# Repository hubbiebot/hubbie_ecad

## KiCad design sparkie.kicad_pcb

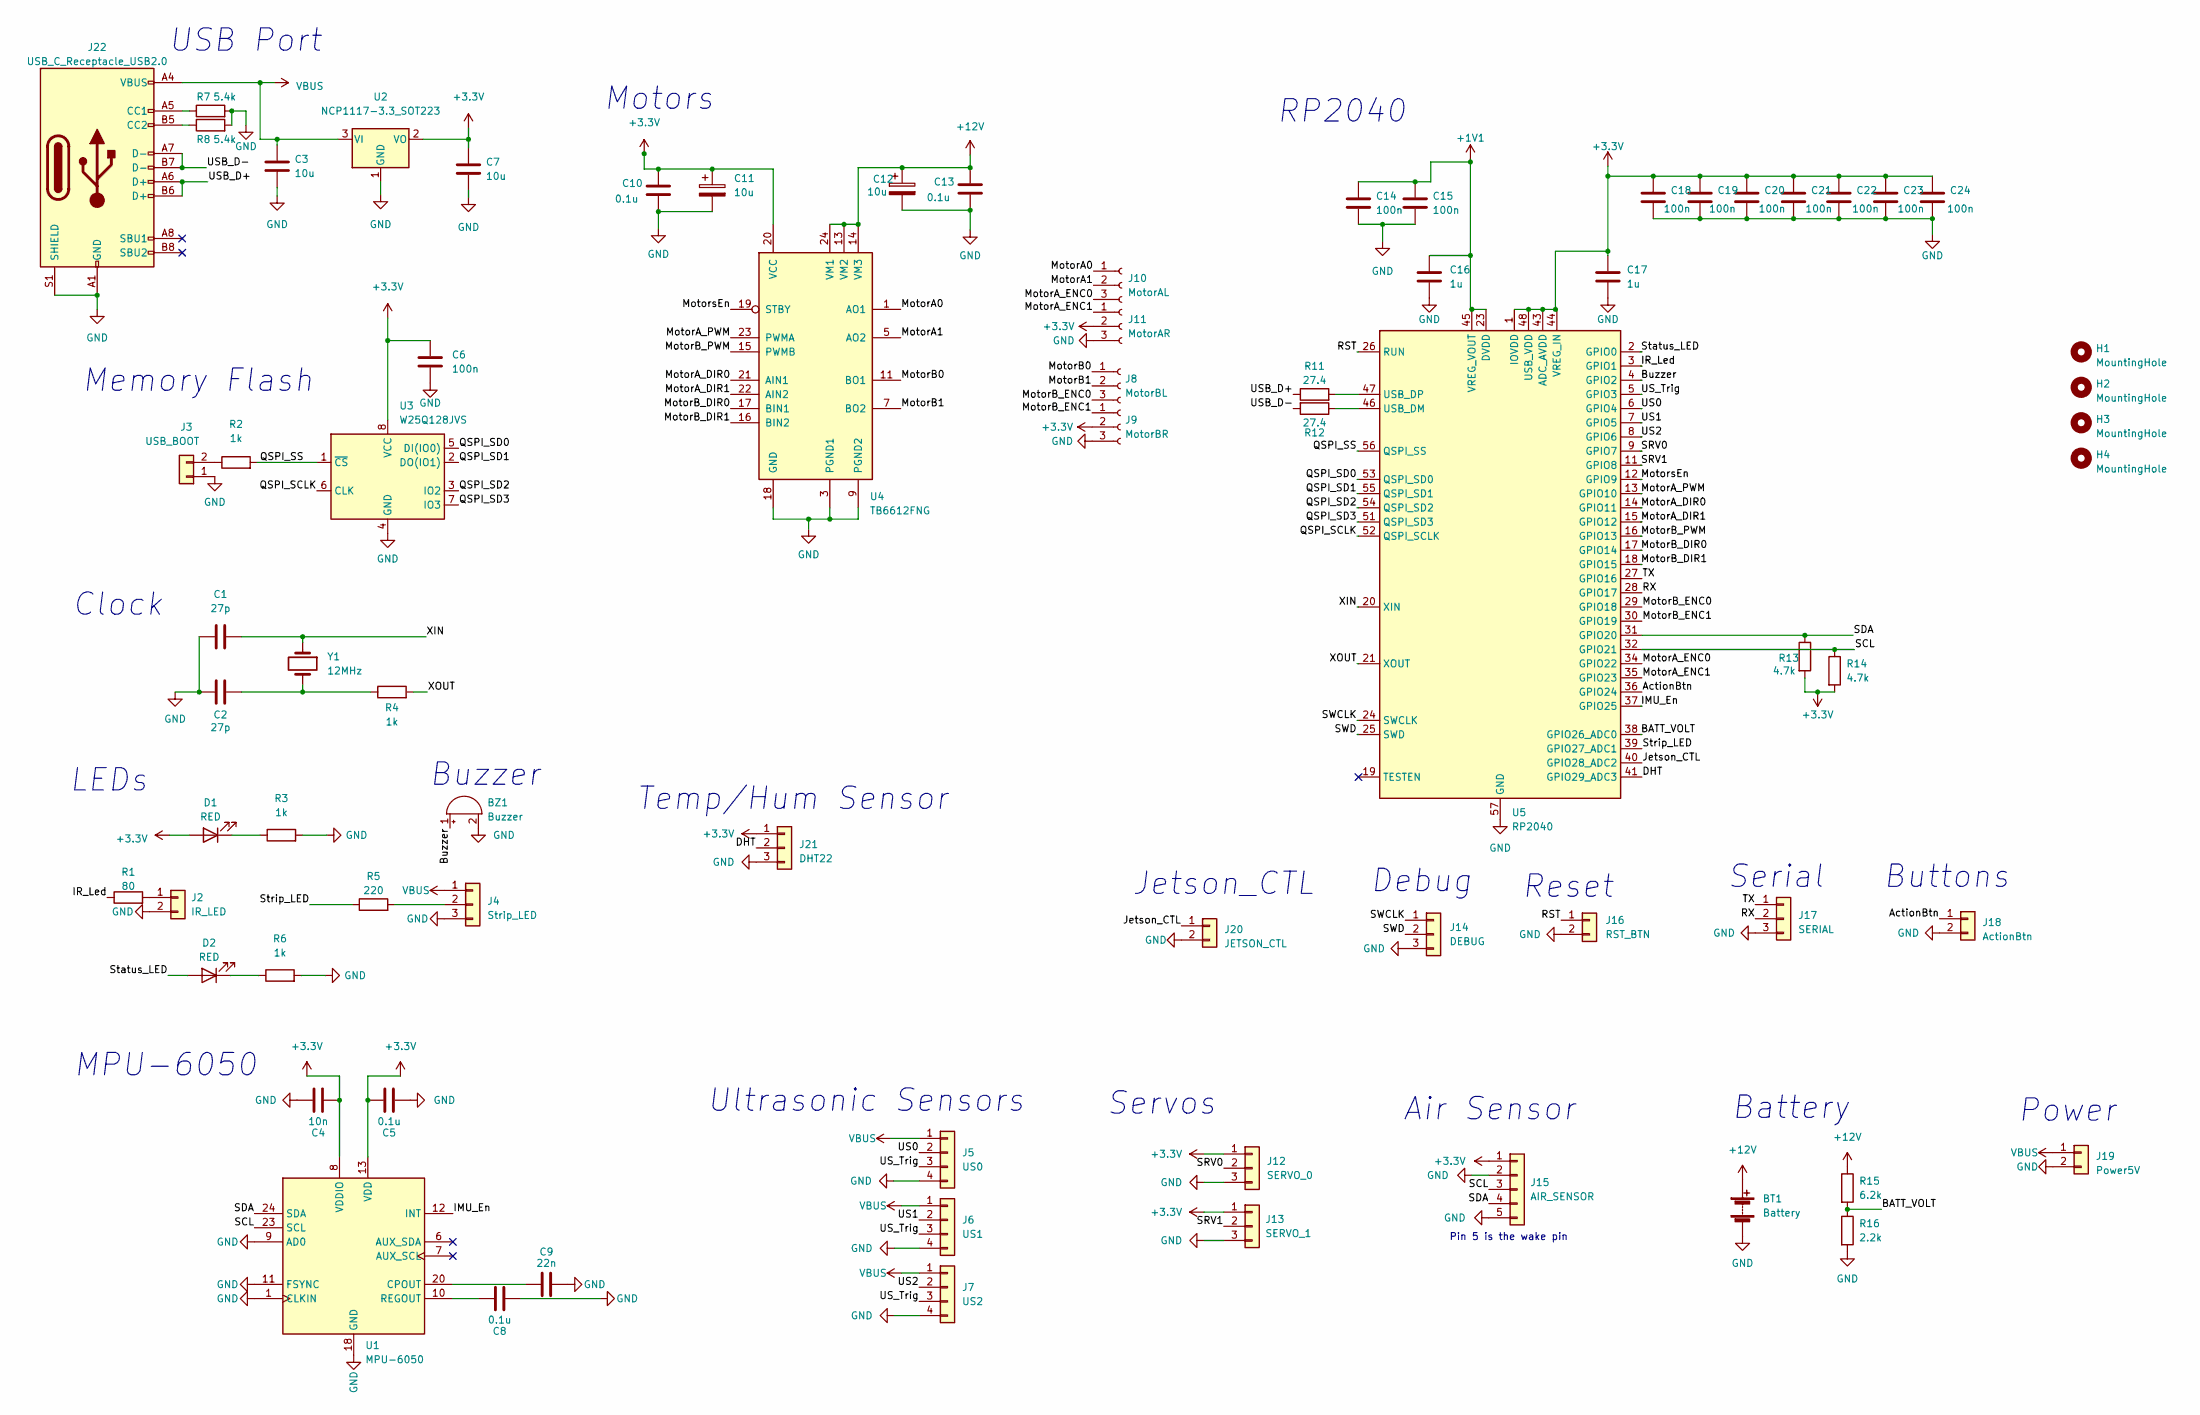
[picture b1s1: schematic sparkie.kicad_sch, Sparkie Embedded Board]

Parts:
BT1: Battery; AMASS_XT60-F_1x02_P7.20mm_Vertical
BZ1: Buzzer; Buzzer_12x9.5RM7.6
C1, C2: 27p; C_0603_1608Metric
C3, C7: 10u; C_0603_1608Metric
C4: 10n; C_0603_1608Metric
C5, C8, C10, C13: 0.1u; C_0603_1608Metric
C6, C14, C15, C18, C19, C20, C21, C22, C23, C24: 100n; C_0603_1608Metric
C9: 22n; C_0603_1608Metric
C11, C12: 10u; CP_Elec_4x5.4
C16, C17: 1u; C_0603_1608Metric
D1, D2: RED; LED_1206_3216Metric
H1, H2, H3, H4: MountingHole; MountingHole_2.2mm_M2
J2: IR_LED; JST_XH_B2B-XH-A_1x02_P2.50mm_Vertical
J3: USB_BOOT; SW_Tactile_SPST_NO_Straight_CK_PTS636Sx25SMTRLFS
J4: Strip_LED; JST_XH_B3B-XH-A_1x03_P2.50mm_Vertical
J5: US0; JST_XH_B4B-XH-A_1x04_P2.50mm_Vertical
J6: US1; JST_XH_B4B-XH-A_1x04_P2.50mm_Vertical
J7: US2; JST_XH_B4B-XH-A_1x04_P2.50mm_Vertical
J8: MotorBL; JST_XH_B3B-XH-A_1x03_P2.50mm_Vertical
J9: MotorBR; JST_XH_B3B-XH-A_1x03_P2.50mm_Vertical
J10: MotorAL; JST_XH_B3B-XH-A_1x03_P2.50mm_Vertical
J11: MotorAR; JST_XH_B3B-XH-A_1x03_P2.50mm_Vertical
J12: SERVO_0; JST_XH_B3B-XH-A_1x03_P2.50mm_Vertical
J13: SERVO_1; JST_XH_B3B-XH-A_1x03_P2.50mm_Vertical
J14: DEBUG; PinSocket_1x03_P2.54mm_Vertical
J15: AIR_SENSOR; JST_XH_B5B-XH-AM_1x05_P2.50mm_Vertical
J16: RST_BTN; SW_Tactile_SPST_NO_Straight_CK_PTS636Sx25SMTRLFS
J17: SERIAL; JST_XH_B3B-XH-A_1x03_P2.50mm_Vertical
J18: ActionBtn; JST_XH_B2B-XH-A_1x02_P2.50mm_Vertical
J19: Power5V; JST_XH_B2B-XH-A_1x02_P2.50mm_Vertical
J20: JETSON_CTL; PinSocket_1x02_P2.54mm_Vertical
J21: DHT22; JST_XH_B3B-XH-A_1x03_P2.50mm_Vertical
J22: USB_C_Receptacle_USB2.0; USB_C_Receptacle_XKB_U262-16XN-4BVC11
R1: 80; R_0603_1608Metric
R2, R3, R4, R6: 1k; R_0603_1608Metric
R5: 220; R_0603_1608Metric
R7, R8: 5.4k; R_0603_1608Metric
R11, R12: 27.4; R_0603_1608Metric
R13, R14: 4.7k; R_0603_1608Metric
R15: 6.2k; R_0603_1608Metric
R16: 2.2k; R_0603_1608Metric
U1: MPU-6050; InvenSense_QFN-24_4x4mm_P0.5mm
U2: NCP1117-3.3_SOT223; SOT-223-3_TabPin2
U3: W25Q128JVS; SOIC-8_5.23x5.23mm_P1.27mm
U4: TB6612FNG; SSOP-24_5.3x8.2mm_P0.65mm
U5: RP2040; QFN-56-1EP_7x7mm_P0.4mm_EP3.2x3.2mm
Y1: 12MHz; Crystal_SMD_5032-4Pin_5.0x3.2mm

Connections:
+1V1: C14.1, C15.1, C16.1, U5.23 (DVDD), U5.45 (VREG_VOUT), U5.50 (DVDD)
+3.3V: C4.2, C5.1, C6.1, C7.1, C10.1, C11.1, C17.1, C18.1, C19.1, C20.1, C21.1, C22.1, C23.1, C24.1, D1.2 (A), J9.2, J11.2, J12.1, J13.1, J15.1, J21.1, R13.2, R14.2, U1.8 (VDDIO), U1.13 (VDD), U2.2 (VO), U3.8 (VCC), U4.20 (VCC), U5.1 (IOVDD), U5.10 (IOVDD), U5.22 (IOVDD), U5.33 (IOVDD), U5.42 (IOVDD), U5.43 (ADC_AVDD), U5.44 (VREG_IN), U5.48 (USB_VDD), U5.49 (IOVDD)
+12V: BT1.1 (+), C12.1, C13.1, R15.1, U4.13 (VM2), U4.14 (VM3), U4.24 (VM1)
/ActionBtn: J18.1, U5.36 (GPIO24)
/BATT_VOLT: R15.2, R16.1, U5.38 (GPIO26_ADC0)
/Buzzer: BZ1.1 (-), U5.4 (GPIO2)
/DHT: J21.2, U5.41 (GPIO29_ADC3)
/IMU_En: U1.12 (INT), U5.37 (GPIO25)
/IR_Led: R1.1, U5.3 (GPIO1)
/Jetson_CTL: J20.1, U5.40 (GPIO28_ADC2)
/MotorA0: J10.1, U4.1 (AO1), U4.2 (AO1)
/MotorA1: J10.2, U4.5 (AO2), U4.6 (AO2)
/MotorA_DIR0: U4.21 (AIN1), U5.14 (GPIO11)
/MotorA_DIR1: U4.22 (AIN2), U5.15 (GPIO12)
/MotorA_ENC0: J10.3, U5.34 (GPIO22)
/MotorA_ENC1: J11.1, U5.35 (GPIO23)
/MotorA_PWM: U4.23 (PWMA), U5.13 (GPIO10)
/MotorB0: J8.1, U4.11 (BO1), U4.12 (BO1)
/MotorB1: J8.2, U4.7 (BO2), U4.8 (BO2)
/MotorB_DIR0: U4.17 (BIN1), U5.17 (GPIO14)
/MotorB_DIR1: U4.16 (BIN2), U5.18 (GPIO15)
/MotorB_ENC0: J8.3, U5.29 (GPIO18)
/MotorB_ENC1: J9.1, U5.30 (GPIO19)
/MotorB_PWM: U4.15 (PWMB), U5.16 (GPIO13)
/MotorsEn: U4.19 (STBY), U5.12 (GPIO9)
/QSPI_SCLK: U3.6 (CLK), U5.52 (QSPI_SCLK)
/QSPI_SD0: U3.5 (DI(IO0)), U5.53 (QSPI_SD0)
/QSPI_SD1: U3.2 (DO(IO1)), U5.55 (QSPI_SD1)
/QSPI_SD2: U3.3 (IO2), U5.54 (QSPI_SD2)
/QSPI_SD3: U3.7 (IO3), U5.51 (QSPI_SD3)
/QSPI_SS: R2.2, U3.1 (~CS), U5.56 (QSPI_SS)
/RST: J16.1, U5.26 (RUN)
/RX: J17.2, U5.28 (GPIO17)
/SCL: J15.3, R14.1, U1.23 (SCL), U5.32 (GPIO21)
/SDA: J15.4, R13.1, U1.24 (SDA), U5.31 (GPIO20)
/SRV0: J12.2, U5.9 (GPIO7)
/SRV1: J13.2, U5.11 (GPIO8)
/SWCLK: J14.1, U5.24 (SWCLK)
/SWD: J14.2, U5.25 (SWD)
/Status_LED: D2.2 (A), U5.2 (GPIO0)
/Strip_LED: R5.1, U5.39 (GPIO27_ADC1)
/TX: J17.1, U5.27 (GPIO16)
/US0: J5.2, U5.6 (GPIO4)
/US1: J6.2, U5.7 (GPIO5)
/US2: J7.2, U5.8 (GPIO6)
/USB_D+: J22.A6 (D+), J22.B6 (D+), R11.1
/USB_D-: J22.A7 (D-), J22.B7 (D-), R12.2
/US_Trig: J5.3, J6.3, J7.3, U5.5 (GPIO3)
/XIN: C1.2, U5.20 (XIN), Y1.1
/XOUT: R4.2, U5.21 (XOUT)
GND: BT1.2 (-), BZ1.2 (+), C1.1, C2.1, C3.2, C4.1, C5.2, C6.2, C7.2, C8.2, C9.1, C10.2, C11.2, C12.2, C13.2, C14.2, C15.2, C16.2, C17.2, C18.2, C19.2, C20.2, C21.2, C22.2, C23.2, C24.2, J2.2, J3.1, J4.3, J5.4, J6.4, J7.4, J9.3, J11.3, J12.3, J13.3, J14.3, J15.2, J15.5, J16.2, J17.3, J18.2, J19.2, J20.2, J21.3, J22.A1 (GND), J22.A12 (GND), J22.B1 (GND), J22.B12 (GND), J22.S1 (SHIELD), R3.2, R6.2, R7.2, R8.2, R16.2, U1.1 (CLKIN), U1.9 (AD0), U1.11 (FSYNC), U1.18 (GND), U2.1 (GND), U3.4 (GND), U4.3 (PGND1), U4.4 (PGND1), U4.9 (PGND2), U4.10 (PGND2), U4.18 (GND), U5.57 (GND)
unnamed: C2.2, R4.1, Y1.2
unnamed: D1.1 (K), R3.1
unnamed: D2.1 (K), R6.1
unnamed: J2.1, R1.2
unnamed: J3.2, R2.1
unnamed: J4.2, R5.2
unnamed: J22.A5 (CC1), R7.1
unnamed: J22.B5 (CC2), R8.1
unnamed: C9.2, U1.20 (CPOUT)
unnamed: C8.1, U1.10 (REGOUT)
unnamed: R12.1, U5.46 (USB_DM)
unnamed: R11.2, U5.47 (USB_DP)
VBUS: C3.1, J4.1, J5.1, J6.1, J7.1, J19.1, J22.A4 (VBUS), J22.A9 (VBUS), J22.B4 (VBUS), J22.B9 (VBUS), U2.3 (VI)

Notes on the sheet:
Pin 5 is the wake pin
Jetson_CTL
Power
Debug
Buzzer
Memory Flash
Reset
Ultrasonic Sensors
Servos
Temp/Hum Sensor
RP2040
Buttons
Clock
MPU-6050
Serial
Motors
Battery
USB Port
LEDs
Air Sensor

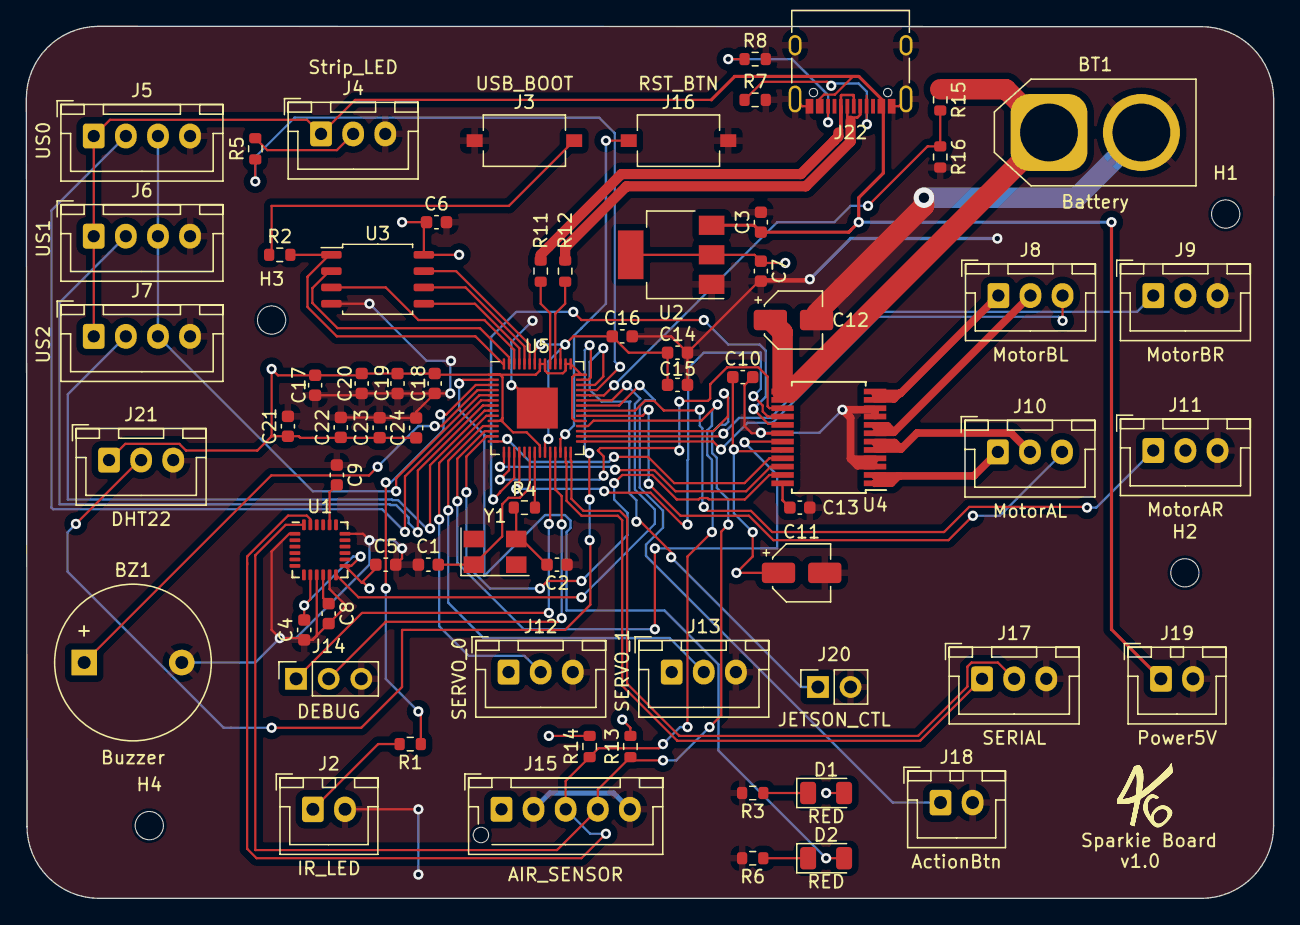
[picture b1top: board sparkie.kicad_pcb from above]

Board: 2 copper layers, 97.1 x 67.9 mm, 73 parts (0 on the bottom side), 64 nets.

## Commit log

2023-06-15 Add html page workflow
2023-06-20 Updated ultrasonic sensor vcc to 5v
2023-06-23 Add usb c support and fix wrong voltage sources
2023-06-23 Changed bom folder to web
2023-06-23 Update github pages
2023-06-23 Wrong path fix
2023-06-23 Group ecad folder setup
2023-06-23 Moved web content to ecad folder
2023-07-21 Update wrong capacitor values (C4 and C9)
2023-07-21 Update schematic and ibom files
2023-08-22 Changed name to 'Sparkie'
2023-08-22 Removed rename action from pages workflow
